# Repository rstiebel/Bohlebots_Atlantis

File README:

This is the Bohlebots Atlantis folder.
It contains all the files that have been used to create the robocup 2vs2 vision soccer bots

Also have a look at the main Bohlebots Github:
https://github.com/bohlebots/soccer

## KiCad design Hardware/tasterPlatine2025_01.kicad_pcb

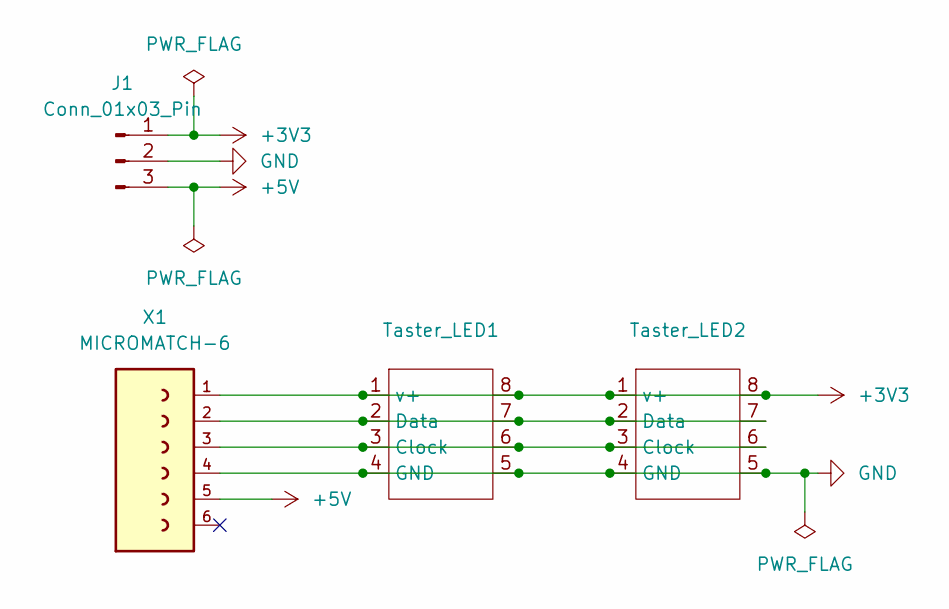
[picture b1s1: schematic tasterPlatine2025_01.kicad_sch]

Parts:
J1: Conn_01x03_Pin; PinHeader_1x03_P2.54mm_Vertical
Taster_LED1, Taster_LED2: TASTER_LED
X1: MICROMATCH-6

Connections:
+3V3: J1.1, Taster_LED1.1 (v+), Taster_LED1.8, Taster_LED2.1 (v+), Taster_LED2.8, X1.1
+5V: J1.3, X1.5
GND: J1.2, Taster_LED1.4 (GND), Taster_LED1.5, Taster_LED2.4 (GND), Taster_LED2.5, X1.4
unnamed: Taster_LED1.3 (Clock), Taster_LED1.6, Taster_LED2.3 (Clock), Taster_LED2.6, X1.3
unnamed: Taster_LED1.2 (Data), Taster_LED1.7, Taster_LED2.2 (Data), Taster_LED2.7, X1.2

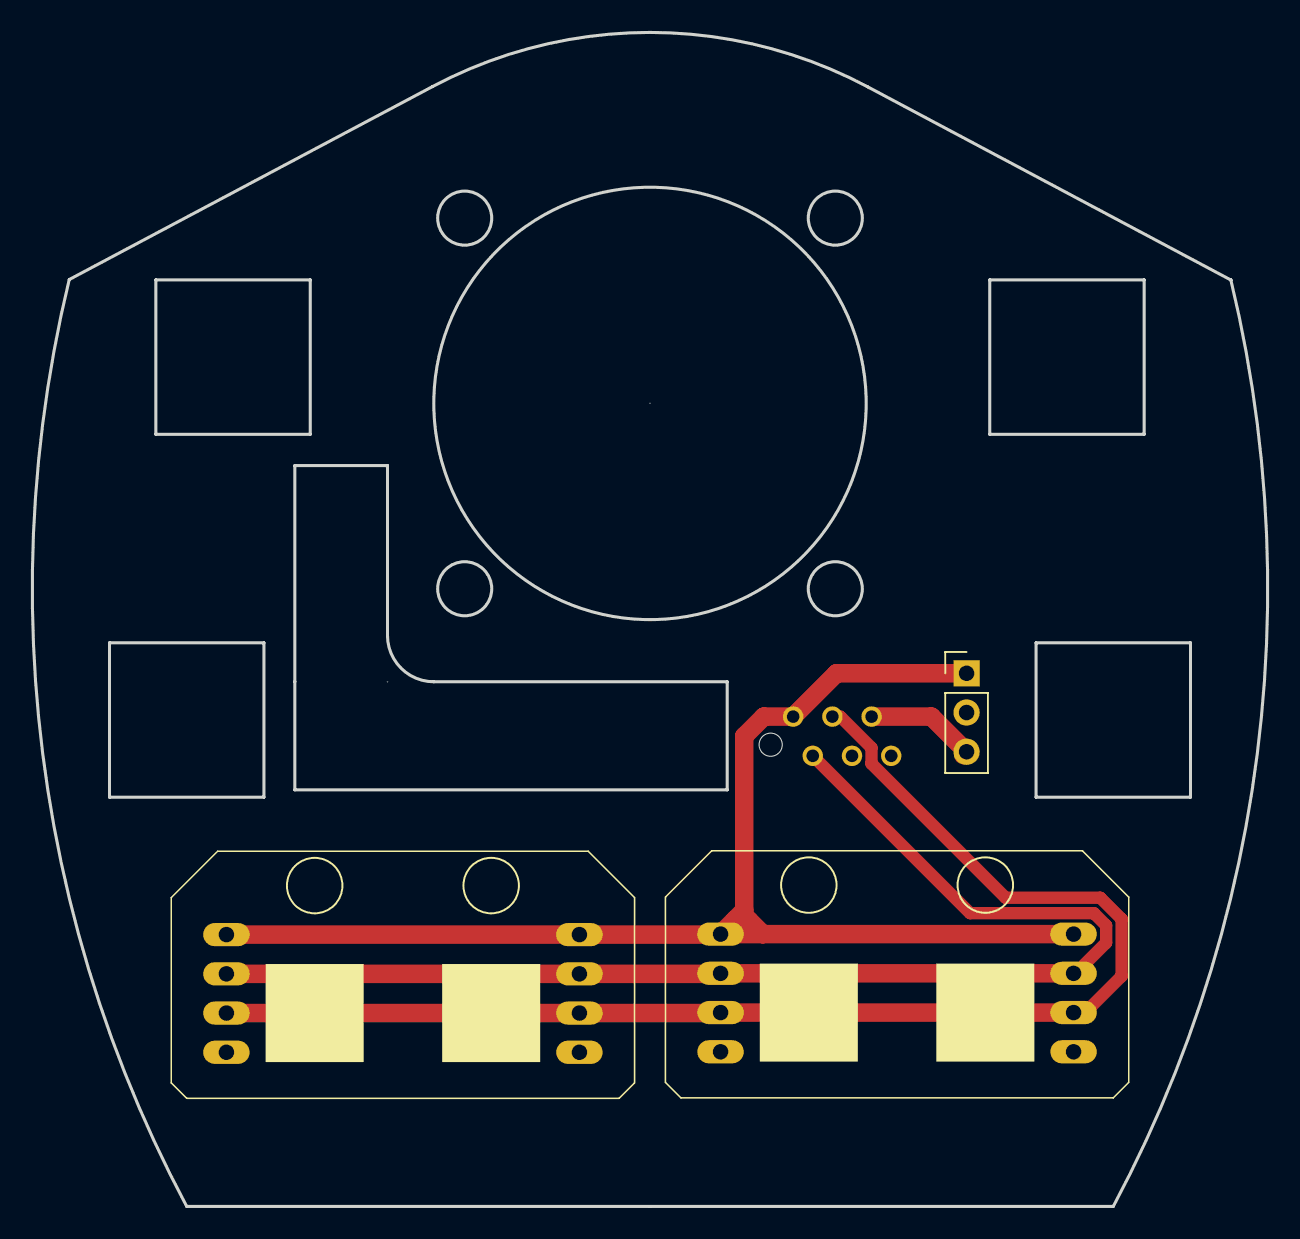
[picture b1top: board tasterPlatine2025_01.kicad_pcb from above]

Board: 2 copper layers, 80.0 x 76.0 mm, 4 parts (1 on the bottom side), 5 nets.

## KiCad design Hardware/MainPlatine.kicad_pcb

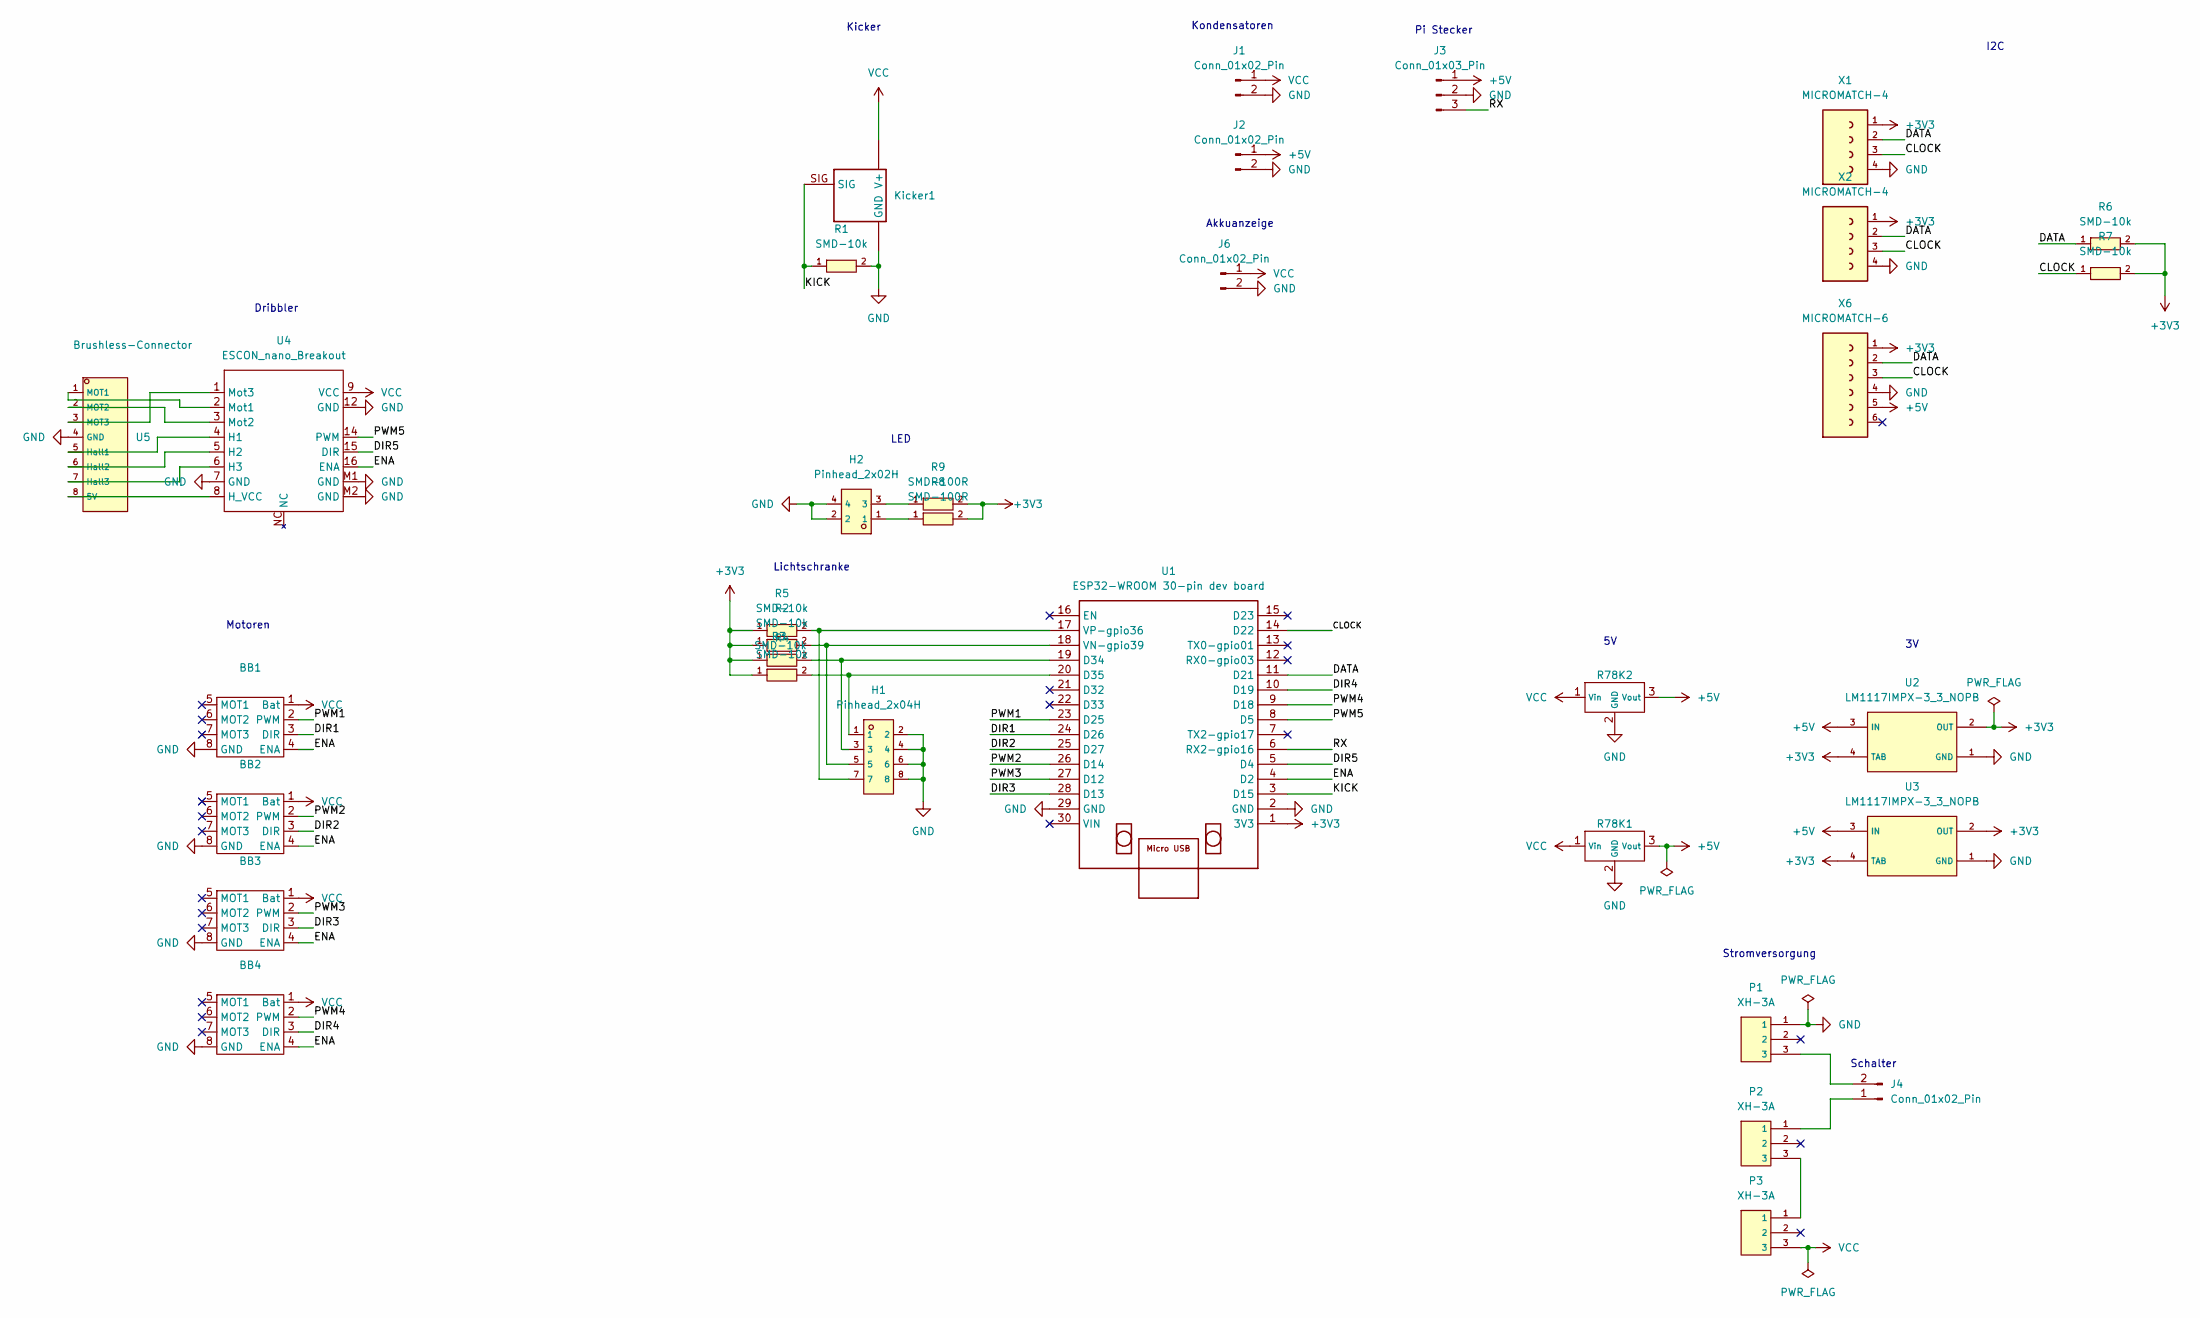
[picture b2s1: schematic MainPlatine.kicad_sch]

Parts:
BB1, BB2, BB3, BB4: ESCON_nano_breakout_stie
H1: Pinhead_2x04H; PinHeader_2x04_P2.54mm_Vertical; LCSC C706885
H2: Pinhead_2x02H; PinHeader_2x02_P2.54mm_Vertical; LCSC C706883
J1, J2, J4, J6: Conn_01x02_Pin; PinHeader_1x02_P2.54mm_Vertical
J3: Conn_01x03_Pin; PinHeader_1x03_P2.54mm_Vertical
Kicker1: KICKER
P1, P2, P3: XH-3A; CONN-TH_XH-3A; LCSC C2316
R1, R2, R3, R4, R5, R6, R7: SMD-10k; R0603; LCSC C25804
R8, R9: SMD-100R; R0603; LCSC C22775
R78K1, R78K2: R785K
U1: ESP32-WROOM 30-pin dev board; MODULE_ESP32_DEVKIT_V1
U2, U3: LM1117IMPX-3_3_NOPB; SOT-223_L6.5-W3.5-P2.30-LS7.0-BR; LCSC C23984
U4: ESCON_nano_Breakout; ESCON 24-2 Breakout
U5: Brushless-Connector; CONN-TH_B8B-PH-K-S-LF-SN; LCSC C157974
X1, X2: MICROMATCH-4
X6: MICROMATCH-6

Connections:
+3V3: R2.1, R3.1, R4.1, R5.1, R6.2, R7.2, R8.2, R9.2, U1.1 (3V3), U2.2 (OUT), U2.4 (TAB), U3.2 (OUT), U3.4 (TAB), X1.1, X2.1, X6.1
+5V: J2.1, J3.1, R78K1.3 (Vout), R78K2.3 (Vout), U2.3 (IN), U3.3 (IN), X6.5
/CLOCK: R7.1, U1.14 (D22), X1.3, X2.3, X6.3
/DATA: R6.1, U1.11 (D21), X1.2, X2.2, X6.2
/DIR1: BB1.3 (DIR), U1.24 (D26)
/DIR2: BB2.3 (DIR), U1.25 (D27)
/DIR3: BB3.3 (DIR), U1.28 (D13)
/DIR4: BB4.3 (DIR), U1.10 (D19)
/DIR5: U1.5 (D4), U4.15 (DIR)
/ENA: BB1.4 (ENA), BB2.4 (ENA), BB3.4 (ENA), BB4.4 (ENA), U1.4 (D2), U4.16 (ENA)
/KICK: Kicker1.SIG, R1.1, U1.3 (D15)
/PWM1: BB1.2 (PWM), U1.23 (D25)
/PWM2: BB2.2 (PWM), U1.26 (D14)
/PWM3: BB3.2 (PWM), U1.27 (D12)
/PWM4: BB4.2 (PWM), U1.9 (D18)
/PWM5: U1.8 (D5), U4.14 (PWM)
/RX: J3.3, U1.6 (RX2-gpio16)
GND: BB1.8 (GND), BB2.8 (GND), BB3.8 (GND), BB4.8 (GND), H1.2, H1.4, H1.6, H1.8, H2.2, H2.4, J1.2, J2.2, J3.2, J6.2, Kicker1.GND1 (GND), Kicker1.GND2 (GND), Kicker1.GND3 (GND), Kicker1.GND4 (GND), Kicker1.GND5 (GND), Kicker1.GND6 (GND), Kicker1.GND7 (GND), Kicker1.GND8 (GND), P1.1, R1.2, R78K1.2 (GND), R78K2.2 (GND), U1.2 (GND), U1.29 (GND), U2.1 (GND), U3.1 (GND), U4.7 (GND), U4.12 (GND), U4.13 (GND), U4.M1 (GND), U4.M2 (GND), U5.4 (GND), X1.4, X2.4, X6.4
unnamed: H2.1, R8.1
unnamed: H2.3, R9.1
unnamed: J4.1, P2.1
unnamed: J4.2, P1.3
unnamed: P2.3, P3.1
unnamed: H1.3, R3.2, U1.19 (D34)
unnamed: H1.1, R4.2, U1.20 (D35)
unnamed: H1.5, R2.2, U1.18 (VN-gpio39)
unnamed: H1.7, R5.2, U1.17 (VP-gpio36)
unnamed: U4.4 (H1), U5.5 (Hall1)
unnamed: U4.5 (H2), U5.6 (Hall2)
unnamed: U4.6 (H3), U5.7 (Hall3)
unnamed: U4.8 (H_VCC), U5.8 (5V)
unnamed: U4.2 (Mot1), U5.1 (MOT1)
unnamed: U4.3 (Mot2), U5.2 (MOT2)
unnamed: U4.1 (Mot3), U5.3 (MOT3)
VCC: BB1.1 (Bat), BB2.1 (Bat), BB3.1 (Bat), BB4.1 (Bat), J1.1, J6.1, Kicker1.V+1 (V+), Kicker1.V+2 (V+), Kicker1.V+3 (V+), P3.3, R78K1.1 (Vin), R78K2.1 (Vin), U4.9 (VCC), U4.10 (VCC), U4.11 (VCC)

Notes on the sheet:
I2C
Kondensatoren
Stromversorgung
Pi Stecker
Schalter
Dribbler
Kicker
LED
Akkuanzeige
Motoren
Lichtschranke

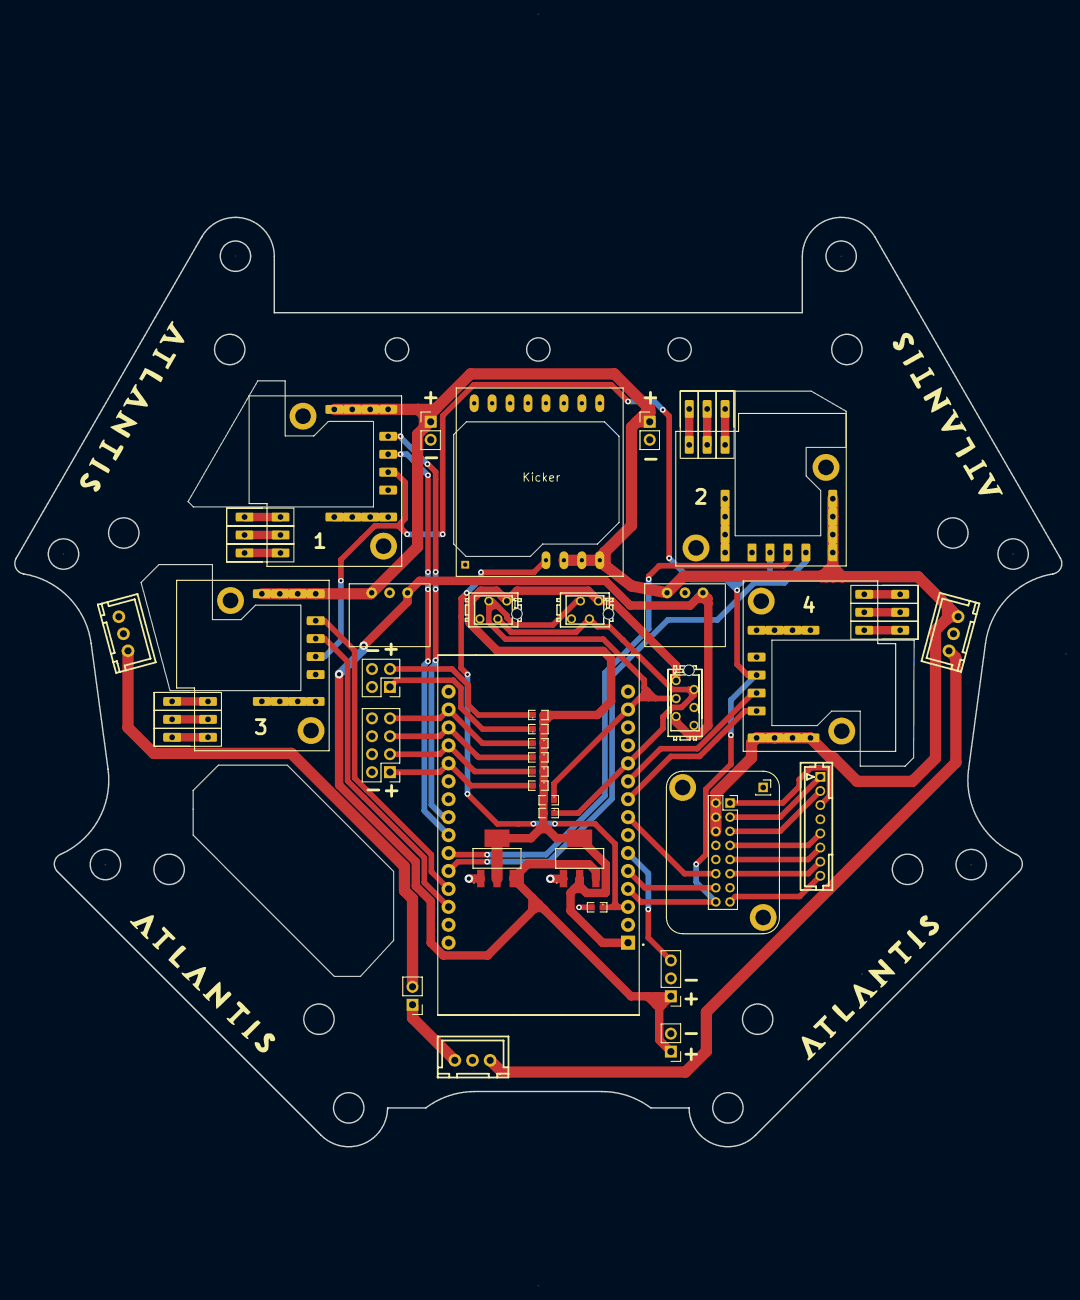
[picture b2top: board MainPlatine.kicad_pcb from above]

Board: 2 copper layers, 148.2 x 131.6 mm, 34 parts (0 on the bottom side), 35 nets.
